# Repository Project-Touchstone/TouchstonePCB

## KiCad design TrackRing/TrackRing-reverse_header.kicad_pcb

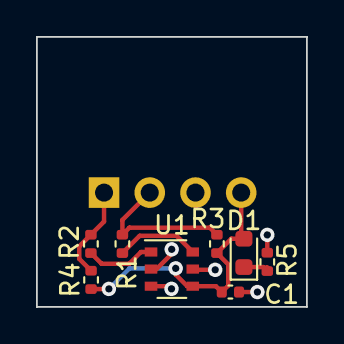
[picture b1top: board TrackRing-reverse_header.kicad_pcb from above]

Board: 2 copper layers, 15.0 x 15.0 mm, 9 parts (1 on the bottom side), 7 nets.

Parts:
C1: 0.1uF; C_0402_1005Metric
D1: LED; LED_0603_1608Metric
J1: Conn_01x04; PinSocket_1x04_P2.54mm_Horizontal
R1, R2: 100; R_0402_1005Metric
R3, R4: 1.2K; R_0402_1005Metric
R5: 500; R_0402_1005Metric
U1: TLV493D-A1B6; TSOP-6_1.65x3.05mm_P0.95mm

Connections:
/SCL: J1.4, R2.1, R4.2
/SDA: J1.3, R1.1, R3.2
/VCC: C1.2, D1.2 (A), J1.1, R3.1, R4.1, U1.4 (VCC)
GND: C1.1, J1.2, R5.2, U1.2 (GND), U1.3 (GND), U1.5 (GND)
unnamed: D1.1 (K), R5.1
unnamed: R2.2, U1.1 (SCL)
unnamed: R1.2, U1.6 (SDA)

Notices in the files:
TrackRing/TrackRing-reverse_header.kicad_pcb:
©CGR
